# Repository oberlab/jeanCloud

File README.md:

<p align="center">
<h1 align="center">jeanCloud</h1>
<h3 align="center">Your personal cloud (alarm) clock</h3>
</p>

<br>
<br>

### How to set up your JeanCloud in your home network

1. Connect your JeanCloud to power
2. Wait until the JeanCloud WiFi appears
3. Connect to the JeanCloud WiFi and enter 192.168.4.1 into your web browser (NO GOOGLE SEARCH)
4. You should see a web interface in which you can enter the name and password of your home WiFi
5. After you press "save" the JeanCloud WiFi should disappear and your JeanCloud connects to your home WiFi
6. You can access the web interface of your JeanCloud by entering its IP address into your web browser (with a device which is in the SAME network). You can identify the IP address of your JeanCloud either by using any network analysis tool (like the [app fing](https://www.fing.com/products/fing-app)) or looking into your router web interface. Check for connected (generic) devices and identify your JeanCloud (sometimes the device is named "espressif")

### Jean Cloud mit dem Heimnetzwerk verbinden

1. Versorge deinen JeanCloud mit Strom
2. Warte bis das JeanCloud WLan erscheint
3. Verbinde dich mit dem JeanCloud WLan und gebe 192.168.4.1 in der Adresszeile deines Webbrowsers ein (KEINE GOOGLE SUCHE)
4. Du solltest jetzt ein Webinterface sehen in dem du den Namen und das Passwort deines Heimnetzwerks eingeben kannst
5. Wenn du jetzt "Speichern" drückst, sollte das JeanCloud WLan verschwinden und dein JeanCloud sich mit deinem Heimnetzwerk verbinden
6. Du kannst jetzt das Webinterface zur Steuerung des Lichts etc. aufrufen indem du die IP Adresse deines JeanClouds in der Adresszeile deines Webbrowsers eingibst. Du kannst die IP Adresse deines JeanClouds entweder durch ein Netzwerkanalyse Tool wie z.B. die [App fing](https://www.fing.com/products/fing-app) oder über das Webinteface von deinem Heimrouter (schau unter verbundene Geräte) herausfinden.

### Electronic connections

**Display:** CLK to pin 18, DIO to pin 5, 5V to 3V3, GND to GND
**LED-Strip:** Data to pin 14, 5V to 5V or Vin, GND to GND
**Buzzer:** one leg to pin 32, one leg to GND (use the one of the display)

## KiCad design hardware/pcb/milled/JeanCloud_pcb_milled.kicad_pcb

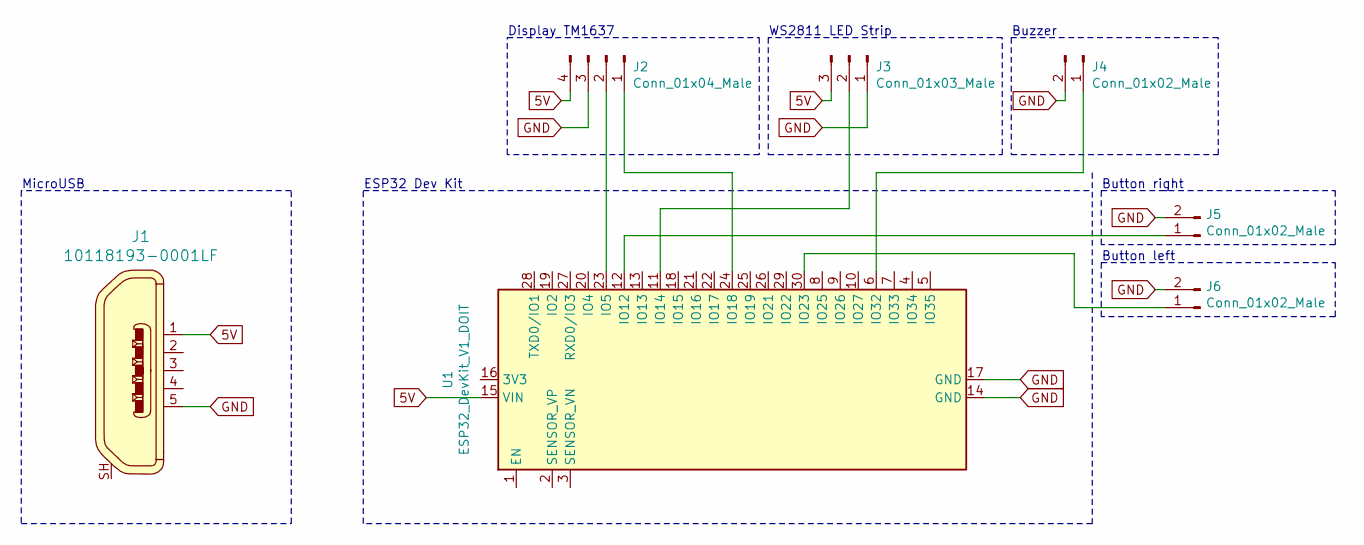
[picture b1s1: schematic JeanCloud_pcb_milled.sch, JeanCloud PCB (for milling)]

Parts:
J1: 10118193-0001LF; USB_Micro_B_Female_10118193-0001LF; MPN 10118193-0001LF; Digi-Key_PN 609-4616-1-ND
J2: Conn_01x04_Male; PinHeader_1x04_P2.54mm_Vertical
J3: Conn_01x03_Male; PinHeader_1x03_P2.54mm_Vertical
J4, J5, J6: Conn_01x02_Male; PinHeader_1x02_P2.54mm_Vertical
U1: ESP32_DevKit_V1_DOIT; esp32_devkit_v1_doit

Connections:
5V: J1.1, J2.4, J3.3, U1.15 (VIN)
GND: J1.5, J2.3, J3.1, J4.2, J5.2, J6.2, U1.14 (GND), U1.17 (GND)
unnamed: J2.1, U1.24 (IO18)
unnamed: J2.2, U1.23 (IO5)
unnamed: J3.2, U1.11 (IO14)
unnamed: J4.1, U1.6 (IO32)
unnamed: J5.1, U1.12 (IO12)
unnamed: J6.1, U1.30 (IO23)

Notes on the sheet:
Display TM1637
WS2811 LED Strip
Buzzer
Button right
Button left
ESP32 Dev Kit
MicroUSB

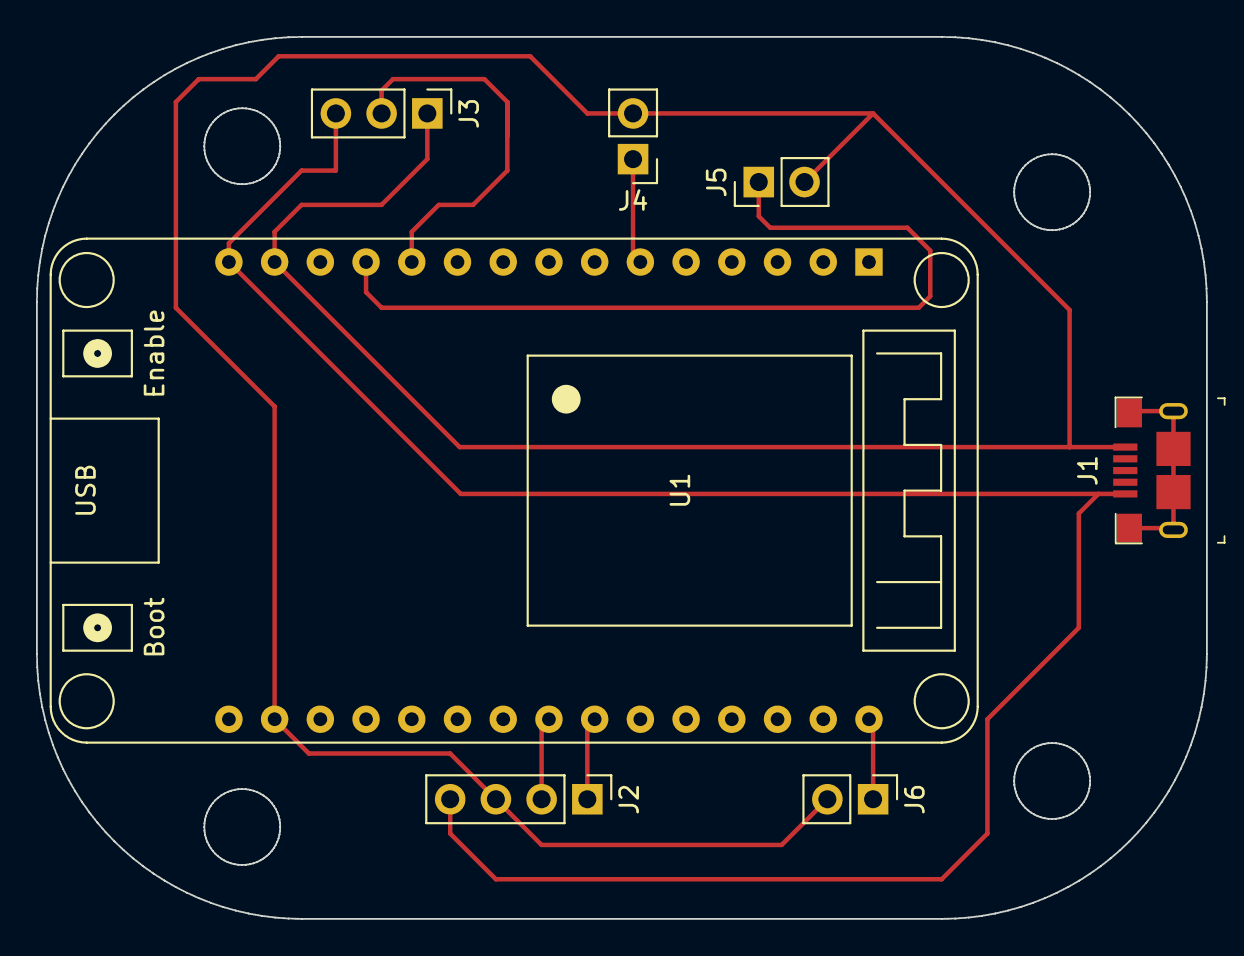
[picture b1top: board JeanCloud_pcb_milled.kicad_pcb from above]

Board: 2 copper layers, 65.0 x 49.0 mm, 7 parts (0 on the bottom side), 8 nets.

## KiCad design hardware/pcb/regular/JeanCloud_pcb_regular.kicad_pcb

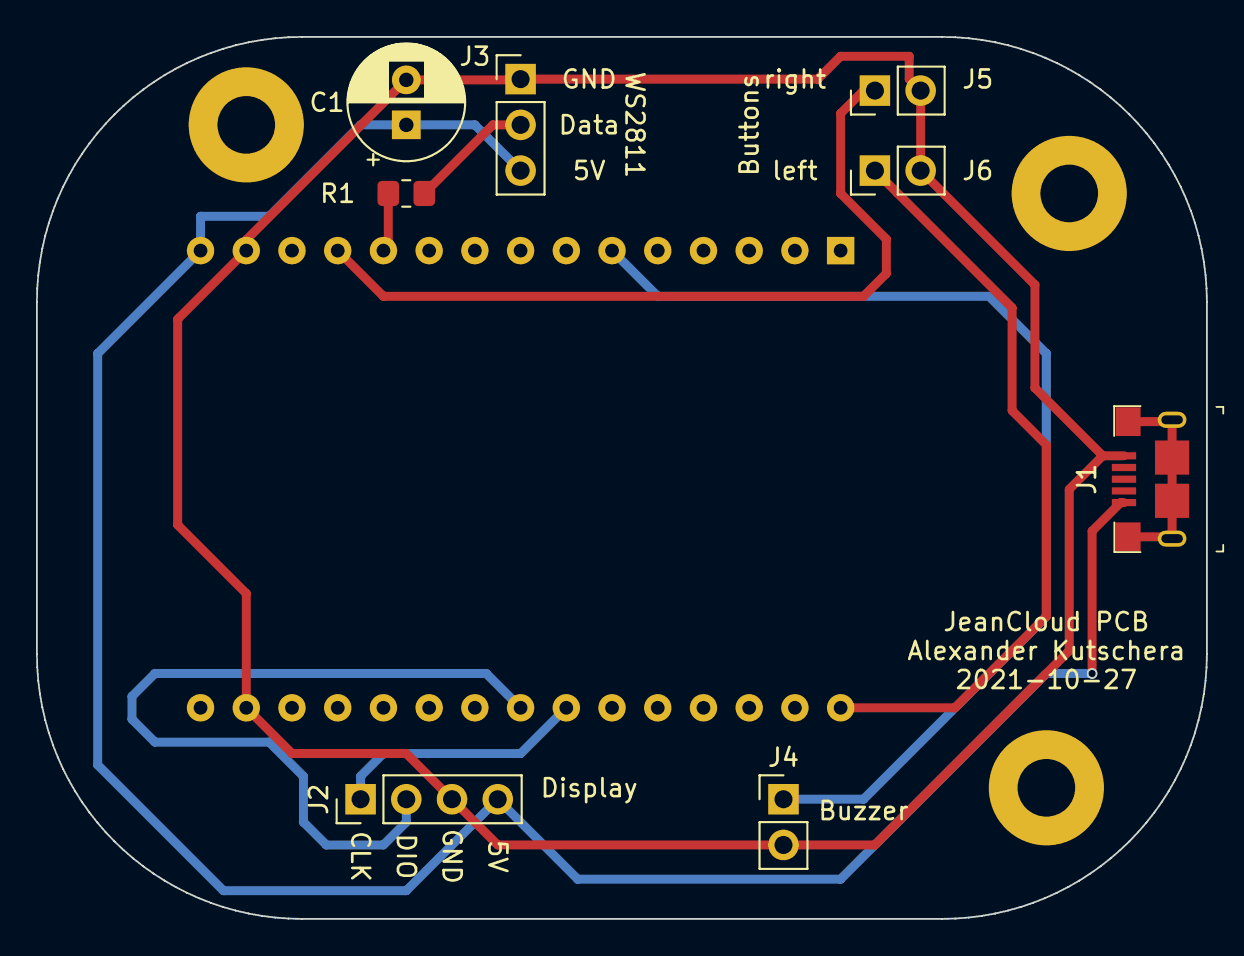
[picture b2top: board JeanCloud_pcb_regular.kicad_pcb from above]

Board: 2 copper layers, 65.0 x 49.0 mm, 12 parts (0 on the bottom side), 9 nets.

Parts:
 : MountingHole_3.2mm_M3_Pad
 #2,  #3: MountingHole_3.2mm_M3_Pad
 #4: ESP32_DevKit_V1_DOIT; esp32_devkit_v1_doit
C1: CP; CP_Radial_D6.3mm_P2.50mm
J1: 10118193-0001LF; USB_Micro_B_Female_10118193-0001LF
J2: Conn_01x04_Male; PinHeader_1x04_P2.54mm_Vertical
J3: Conn_01x03_Male; PinHeader_1x03_P2.54mm_Vertical
J4, J5, J6: Conn_01x02_Male; PinHeader_1x02_P2.54mm_Vertical
R1: R; R_0805_2012Metric_Pad1.20x1.40mm_HandSolder

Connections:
5V: #4.15, C1.1, J1.1, J2.4, J3.3
GND: #4.14, #4.17, C1.2, J1.5, J2.3, J3.1, J4.2, J5.2, J6.2
unnamed: #4.24, J2.1
unnamed: #4.23, J2.2
unnamed: J3.2, R1.1
unnamed: #4.6, J4.1
unnamed: #4.12, J5.1
unnamed: #4.30, J6.1
unnamed: #4.11, R1.2

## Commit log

2021-06-24 add licence
2021-06-24 uploaded hardware file (laser), added content to README
2021-06-24 fixed img link in README
2021-06-24 added structure
2021-06-25 update instructions
2021-06-25 fixed img size
2021-06-29 Add Firmware
2021-06-29 added readme
2021-06-29 Add LightController
2021-06-29 added functions
2021-06-29 added index.html and style.css
2021-06-29 Add Webserver
2021-06-29 Add Constructors
2021-06-29 rename, fixxes
2021-06-29 Add Arduino
2021-06-29 Fix Typo
2021-06-29 fixed error in webserver
2021-06-29 Add SPIFFS
2021-06-29 fixed error
2021-06-29 Mo changes
2021-06-29 Add Off funktion
2021-06-29 Fix Umlaute
2021-06-30 uploaded logo
2021-06-30 added color control
2021-06-30 Upgrade Html
2021-06-30 updated code
2021-06-30 Add intenstiy
2021-06-30 I'm smarter than Konsti
2021-06-30 Set RGB
2021-06-30 Better Code
2021-06-30 Cool code
2021-07-04 added alarm functionality
2021-07-04 Add Password Controller
2021-07-04 fixed wifi credential storage
2021-07-04 Add Alarm Configuration
2021-07-04 Added Pointer
2021-07-05 Add Config Endpoint
2021-07-05 Quick Fix
2021-07-05 small error fix
2021-07-07 changed name
2021-07-07 Test
2021-07-07 fixed webserver issues
2021-07-07 Cool Fixes
2021-07-07 Super Cool Fixes
2021-07-07 Final Fixes
2021-07-07 Show Intensity
2021-07-08 updated name
2021-07-27 Add mDNS
2021-07-27 Set Instance Name
2021-07-27 lowercase jeancloud
2021-07-27 add push button thing
2021-08-03 Code Style Changes
2021-08-04 Add one Button
2021-08-07 updated BOM
2021-08-07 updated CloudPush 3D-model
2021-08-10 fixed weird alarm sounds
2021-08-21 Add Animation
2021-08-23 test fade animation
2021-08-23 edit
2021-08-23 finished test animation
2021-08-24 removed fade function becasue it did not work
2021-09-08 added new features
2021-09-13 New Design version.
2021-09-14 add functions
2021-09-14 changed runner timing
2021-09-14 improved 3D-print
2021-09-21 Improved Display spacer, added new box type
2021-09-21 Add Buttons and Display Brightness Controll
2021-09-22 added pulse animation
2021-09-23 GIOP Fix
2021-09-23 Remove Log
2021-10-17 added
2021-10-17 added flash_white
2021-10-17 removed delay from main loop
2021-10-17 Better Alarm
2021-10-17 Add flashing lights
2021-10-17 added footprints to PCB
2021-10-17 Small Fix
2021-10-17 Format Code
2021-10-17 updated SVG
2021-10-23 finished pcb for milling
2021-10-30 finished regular PCB
2022-03-13 Fix TimeZone
2022-03-14 Update hardware designs
2026-05-03 Save local changes before system wipe
